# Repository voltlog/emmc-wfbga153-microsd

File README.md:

# eMMC WFBGA153 to microSD card adapter PCB
This adapter can be used for data recovery purposes by soldering a WFBGA eMMC chip and connecting to a standard microSD card reader for read/write operations or if you would like to build an inexpensive storage device using cheap memory chips obtained from Ebay/Aliexpress or salvaged from other devices. Image below shows the adapter assembled with a Toshiba 4GB eMMC chip.

### What else do you need?
Besides this custom designed PCB you will need a couple of bypass capacitors (0.1-1uF 10V or above in 0603 package) and the eMMC memory chip. eMMC chips in WFBGA153 package are available from every big distributor but if you would like to try your luck with some inexpensive options, check out [this link.](https://voltlog.com/y/pg8ny)

Alternatively you can order this PCB adapter from my [Tindie store](https://www.tindie.com/products/voltlog/emmc-wfbga153-to-microsd-card-adapter-set-of-2/).

More info about this project in [Voltlog #351](https://youtu.be/pFo1xvBqbqs).

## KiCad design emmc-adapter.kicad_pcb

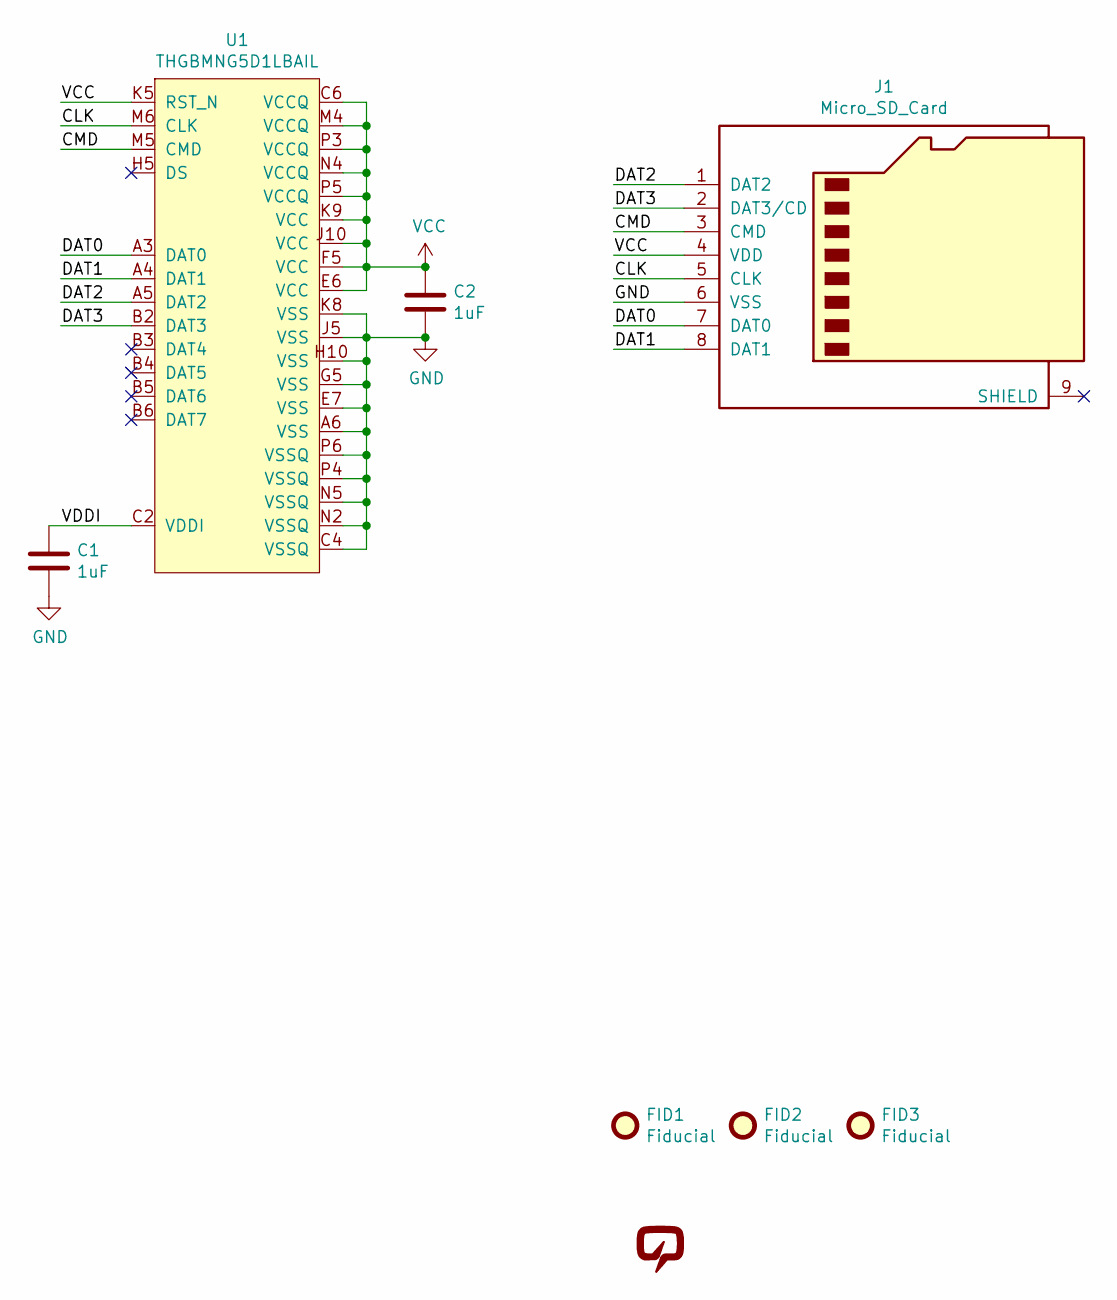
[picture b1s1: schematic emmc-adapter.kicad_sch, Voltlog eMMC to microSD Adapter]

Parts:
C1, C2: 1uF; C_0603_1608Metric
FID1, FID2, FID3: Fiducial; Fiducial_0.5mm_Mask1mm
J1: Micro_SD_Card; microSD_card
U1: THGBMNG5D1LBAIL; WFBGA153
V1: VOLTLOG_LOGO; voltlog_mask_3mm

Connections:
/CLK: J1.5 (CLK), U1.M6 (CLK)
/CMD: J1.3 (CMD), U1.M5 (CMD)
/DAT0: J1.7 (DAT0), U1.A3 (DAT0)
/DAT1: J1.8 (DAT1), U1.A4 (DAT1)
/DAT2: J1.1 (DAT2), U1.A5 (DAT2)
/DAT3: J1.2 (DAT3/CD), U1.B2 (DAT3)
/VDDI: C1.1, U1.C2 (VDDI)
GND: C1.2, C2.2, J1.6 (VSS), U1.A6 (VSS), U1.C4 (VSSQ), U1.E7 (VSS), U1.G5 (VSS), U1.H10 (VSS), U1.J5 (VSS), U1.K8 (VSS), U1.N2 (VSSQ), U1.N5 (VSSQ), U1.P4 (VSSQ), U1.P6 (VSSQ)
VCC: C2.1, J1.4 (VDD), U1.C6 (VCCQ), U1.E6 (VCC), U1.F5 (VCC), U1.J10 (VCC), U1.K5 (RST_N), U1.K9 (VCC), U1.M4 (VCCQ), U1.N4 (VCCQ), U1.P3 (VCCQ), U1.P5 (VCCQ)

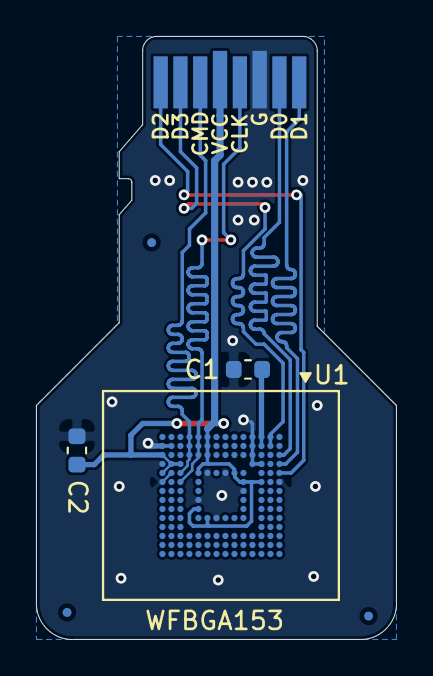
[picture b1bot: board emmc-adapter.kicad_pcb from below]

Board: 2 copper layers, 20.0 x 33.5 mm, 8 parts (7 on the bottom side), 9 nets.

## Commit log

2021-02-16 Initial commit, published project.
2021-02-16 Added image of populated adapter
2021-04-19 Added missing .kicad_pcb file
2024-06-03 Project updated to Kicad v8
